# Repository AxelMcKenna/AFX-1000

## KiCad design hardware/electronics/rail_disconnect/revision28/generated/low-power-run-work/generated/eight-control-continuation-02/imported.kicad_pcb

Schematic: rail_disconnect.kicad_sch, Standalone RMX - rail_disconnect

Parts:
C1, C5, C9, C13, C17, C21, C25, C29, C34, C35, C36, C37, C57, C58, C59, C66, C67, C68, C69, C70, C71, C72, C73, C74, C75, C76, C77: 100nF 16V X7R; C_0805_2012Metric
C2, C3, C6, C7, C10, C11, C14, C15: 10pF 100V C0G 5%; C_0805_2012Metric
C4, C8: 1500uF 35V electrolytic 20% EEUFR1V152S; CP_Radial_D16.0mm_P7.50mm
C12, C16: 220uF 35V electrolytic 20% EEUFR1V221; CP_Radial_D8.0mm_P3.50mm
C20: 1500uF 16V electrolytic 20% EEUFR1C152; CP_Radial_D10.0mm_P5.00mm
C24: 4700uF 16V electrolytic 20% EEUFR1C472; CP_Radial_D16.0mm_P7.50mm
C26: 1uF 16V X7R; C_0805_2012Metric
C27, C28, C30, C31, C32, C33, C53, C54, C55, C56: 100pF 50V C0G 5%; C_0805_2012Metric
C38: 10uF 16V X7R; C_0805_2012Metric
C39, C41, C49, C61, C62, C63, C64, C65: 100nF 50V C0G 5% C1210C104J5GACTU; KEMET_C1210_LevelB
C40, C42, C44, C46, C48, C50, C52: 1uF 50V X7R; C_0805_2012Metric
C43, C45, C47, C51: 47nF 50V C0G 5% C1206C473J5GACTU; KEMET_C1206_LevelB
C60: 10nF 50V C0G 5%; C_0805_2012Metric
C78, C80, C81, C82, C83, C84, C85: 100nF 16V X7R 10% KEMET C0603C104K4RACTU; KEMET_C0603_LevelB
C79: 100nF 16V X7R 10% KEMET C0402C104K4RACTU; KEMET_C0402_LevelB
C86: 100nF 50V X7R C0603C104K5RACTU; AX03_C0603
J1, J3: Header6; PinHeader_1x06_P2.54mm_Vertical
J4: Alpha3079_AWG14_DIG_FORCE; AWG14_Force_2x1_P9mm_Engineering
J5, J6: Header3; PinHeader_1x03_P2.54mm_Vertical
J7, J8, J10, J11: 7466003R; 7466003R_M3_SMT_Annulus_NPTH
J9: E28 CONTROL; PinHeader_1x05_P2.54mm_Vertical
J12: JST B2B-PH-SM4-TB(LF)(SN); JST_B2B_PH_SM4_TB_MechanicalLands
Q1, Q2, Q3, Q4, Q5, Q6, Q7, Q8: CSD18540Q5B; CSD18540Q5B_TI_Q5B
R1, R9, R17, R25: 22 1%; R_0805_2012Metric
R2, R10, R18, R26, R60, R63, R68, R71, R76, R81, R86, R91: 20M 1%; R_0805_2012Metric
R3, R5, R11, R13, R19, R21, R27, R29, R61, R64, R69, R72, R77, R82, R87, R92: 10k 1%; R_0805_2012Metric
R4, R12, R20, R28, R98, R102, R106, R110, R114, R118, R122: 100 1%; R_0805_2012Metric
R6, R7, R14, R15, R22, R23, R30, R31: 15k 1%; R_0805_2012Metric
R8, R16, R24, R32, R40, R48: 47k 1%; R_0805_2012Metric
R49: 150k 0.01% 5ppm; R_0805_2012Metric
R50: 6.2k 0.01% 5ppm; R_0805_2012Metric
R51, R54, R58, R59, R62, R66, R67, R70, R74, R75, R79, R80, R84, R85, R89, R90, R94, R124, R127, R130, R133: 10k 0.01% 5ppm; R_0805_2012Metric
R52, R55: 1k 1%; R_0805_2012Metric
R53: 100k 0.01% 5ppm; R_0805_2012Metric
R56: 143k 0.01% 5ppm; R_0805_2012Metric
R57: 3.3k 0.01% 5ppm; R_0805_2012Metric
R65: 90.9k 0.01% 5ppm; R_0805_2012Metric
R73, R78: 31.6k 0.01% 5ppm; R_0805_2012Metric
R83: 12.4k 0.01% 5ppm; R_0805_2012Metric
R88: 7.5k 0.01% 5ppm; R_0805_2012Metric
R93: 200k 0.1% ERA6AEB204V - COMPLETE1% RECEIVING; R_0805_2012Metric
R95, R99, R103, R107, R111, R115, R119, R125, R128, R131, R134, R136, R141: 10k; R_0805_2012Metric
R96, R100, R104, R108, R112, R116, R120, R140: 47k; R_0805_2012Metric
R97, R101, R117: 2.43k 0.1%; R_0805_2012Metric
R105, R109, R113, R121: 604 0.1%; R_0805_2012Metric
R123, R126, R129, R132: 28.7k 0.01% 5ppm; R_0805_2012Metric
R135: 10k 0.1% 25ppm Panasonic ERA6AEB103V; Resistor_SMD_Panasonic_ERA6A_2012
R137: 11.1k 0.1%; R_0805_2012Metric
R138: 39.2 0.1%; R_0805_2012Metric
R139: 10k 0.1%; R_0805_2012Metric
R142: 15k; R_0805_2012Metric
R143: 15k 0.1% 25ppm Panasonic ERA6AEB153V; Resistor_SMD_Panasonic_ERA6A_2012
U1, U2, U3, U4: SI8751AB-ISR; SOIC-8_3.9x4.9mm_P1.27mm
U7: REF35125QDBVR; SOT-23-6
U8: OPA2333AID; SOIC-8_3.9x4.9mm_P1.27mm
U9, U10: TLV1824DR; SOIC-14_3.9x8.7mm_P1.27mm
U11, U12, U24, U25, U26, U27: SN74LVC08APWR; TSSOP-14_4.4x5mm_P0.65mm
U13, U14, U15, U16, U17, U32, U33: TPS259482LYWP; TPS259482L_YWP0012A
U18: TLV1824PWR; TLV1824_PW0014A
U19, U20: TPS389001DSET; TPS389001_DSE0006A
U21, U22: SN74LVC02APWR; TSSOP-14_4.4x5mm_P0.65mm
U23: SN74LVC32APWR; TSSOP-14_4.4x5mm_P0.65mm
U28: SN74LVC14APWR; SN74LVC14A_PW0014A
U29, U30, U31, U34: SN74AUP2G08DCUR; SN74AUP2G08_DCU0008A
U35, U36, U37, U38, U39, U40, U41, U42: SN74AUP3G17DCUR; SN74LVC3G17_DCU0008A
U43: SN74AUP1G17DCKR; AX03_DCK0005A

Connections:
/5V_DIG: C24.1, J4.1 (5V_DIG), R48.1, R132.1, U15.6 (OUT), U15.11 (OUT), U16.6 (OUT), U16.11 (OUT), U17.6 (OUT), U17.11 (OUT), U33.6 (OUT), U33.11 (OUT)
/5V_DIG_OV_OK: R81.1, R82.2, U10.1 (2OUT), U37.6 (3A)
/5V_DIG_OV_OK_SCHMITT: U11.10 (3B), U37.2 (3Y)
/5V_DIG_OV_REF: R80.2, R81.2, U10.7 (2+)
/5V_DIG_OV_SENSE: C33.1, R78.2, R79.1, U10.6 (2-)
/5V_DIG_SRC: C44.1, C46.1, C48.1, C52.1, J11.1, R78.1, R126.1, U15.5 (IN), U15.12 (IN), U16.5 (IN), U16.12 (IN), U17.5 (IN), U17.12 (IN), U33.5 (IN), U33.12 (IN)
/AGND: C1.2, C4.2, C5.2, C8.1, C9.2, C12.2, C13.2, C16.1, C17.2, C20.2, C21.2, C24.2, C25.2, C26.2, C27.2, C28.2, C29.2, C30.2, C31.2, C32.2, C33.2, C34.2, C35.2, C36.2, C37.2, C38.2, C39.2, C40.2, C41.2, C42.2, C43.2, C44.2, C45.2, C46.2, C47.2, C48.2, C49.2, C50.2, C51.2, C52.2, C53.2, C54.2, C55.2, C56.2, C57.2, C58.2, C59.2, C60.2, C61.2, C62.2, C63.2, C64.2, C65.2, C66.2, C67.2, C68.2, C69.2, C70.2, C71.2, C72.2, C73.2, C74.2, C75.2, C76.2, C77.2, C78.2, C79.2, C80.2, C81.2, C82.2, C83.2, C84.2, C85.2, C86.2, J1.2 (AGND), J3.2 (AGND), J4.2 (AGND), J5.2 (AGND), J6.1 (AGND), J7.1, J8.1, J9.1 (AGND), J12.2 (AGND), R3.2, R5.2, R8.2, R11.2, R13.2, R16.2, R19.2, R21.2, R24.2, R27.2, R29.2, R32.2, R40.2, R48.2, R58.2, R66.2, R74.2, R79.2, R84.2, R89.2, R93.2, R94.2, R96.2, R97.2, R100.2, R101.2, R104.2, R105.2, R108.2, R109.2, R112.2, R113.2, R116.2, R117.2, R120.2, R121.2, R124.2, R127.2, R130.2, R133.2, R139.2, R140.2, R141.2, R142.2, R143.2, U1.4 (GND), U2.4 (GND), U3.4 (GND), U4.4 (GND), U7.1 (GND), U7.2 (GND), U8.3 (IN+_A), U8.4 (V-), U8.5 (IN+_B), U9.12 (V-), U10.12 (V-), U11.7 (GND), U12.7 (GND), U13.2 (OVLO), U13.4 (RCBCTRL), U13.8 (GND), U14.2 (OVLO), U14.4 (RCBCTRL), U14.8 (GND), U15.2 (OVLO), U15.4 (RCBCTRL), U15.8 (GND), U16.2 (OVLO), U16.4 (RCBCTRL), U16.8 (GND), U17.2 (OVLO), U17.4 (RCBCTRL), U17.8 (GND), U18.12 (V-), U19.2 (GND), U20.2 (GND), U21.7 (GND), U22.7 (GND), U22.9 (B), U22.12 (B), U23.7 (GND), U24.7 (GND), U25.7 (GND), U26.7 (GND), U27.7 (GND), U28.7 (GND), U29.4 (GND), U30.4 (GND), U31.4 (GND), U32.2 (OVLO), U32.4 (RCBCTRL), U32.8 (GND), U33.2 (OVLO), U33.4 (RCBCTRL), U33.8 (GND), U34.4 (GND), U35.4 (GND), U36.4 (GND), U37.4 (GND), U38.4 (GND), U39.4 (GND), U40.4 (GND), U41.4 (GND), U42.3 (2A), U42.4 (GND), U42.6 (3A), U43.3 (GND)
/ALL_RAILS_ALLOW: U12.11 (4Y), U21.2 (A), U29.1 (A)
/ANA_OUTPUT_OK: R131.2, U18.14 (UV_OK), U39.3 (2A)
/ANA_OUTPUT_OK_SCHMITT: U24.4 (A), U39.5 (2Y)
/ANA_PG0: R95.1, U13.3 (SPLYGD), U41.3 (2A)
/ANA_PG0_SCHMITT: U31.2 (B), U41.5 (2Y)
/ANA_PG1: R99.1, U14.3 (SPLYGD), U41.6 (3A)
/ANA_PG1_SCHMITT: U34.6 (B), U41.2 (3Y)
/ANA_PG2: R115.1, U32.3 (SPLYGD), U42.1 (1A)
/ANA_PG2_SCHMITT: U26.10 (B), U42.7 (1Y)
/ANA_SOURCE_OK: R125.2, U18.2 (UV_OK), U38.6 (3A)
/ANA_SOURCE_OK_SCHMITT: U24.1 (A), U38.2 (3Y)
/DIG_OUTPUT_OK: R134.2, U18.13 (UV_OK), U39.6 (3A)
/DIG_OUTPUT_OK_SCHMITT: U24.5 (B), U39.2 (3Y)
/DIG_PG0: R103.1, U15.3 (SPLYGD), U40.1 (1A)
/DIG_PG0_SCHMITT: U29.6 (B), U40.7 (1Y)
/DIG_PG1: R107.1, U16.3 (SPLYGD), U40.3 (2A)
/DIG_PG1_SCHMITT: U30.2 (B), U40.5 (2Y)
/DIG_PG2: R111.1, U17.3 (SPLYGD), U40.6 (3A)
/DIG_PG2_SCHMITT: U34.1 (A), U40.2 (3Y)
/DIG_PG3: R119.1, U33.3 (SPLYGD), U41.1 (1A)
/DIG_PG3_SCHMITT: U26.9 (A), U30.6 (B), U41.7 (1Y)
/DIG_SOURCE_OK: R128.2, U18.1 (UV_OK), U39.1 (1A)
/DIG_SOURCE_OK_SCHMITT: U24.2 (B), U39.7 (1Y)
/E28_ALL_CHANNELS_READY: U26.8 (Y), U26.12 (A)
/E28_ANA_0_DVDT: R98.1, U13.7 (DVDT)
/E28_ANA_0_DVDT_CAP: C39.1, R98.2
/E28_ANA_0_ILM: R97.1, U13.9 (ILM)
/E28_ANA_1_DVDT: R102.1, U14.7 (DVDT)
/E28_ANA_1_DVDT_CAP: C41.1, R102.2
/E28_ANA_1_ILM: R101.1, U14.9 (ILM)
/E28_ANA_2_DVDT: R118.1, U32.7 (DVDT)
/E28_ANA_2_DVDT_CAP: C49.1, R118.2
/E28_ANA_2_ILM: R117.1, U32.9 (ILM)
/E28_ANA_ENABLE: R96.1, U13.1 (EN_UVLO), U30.3 (Y)
/E28_ANA_FOLLOW: R100.1, U14.1 (EN_UVLO), U31.7 (Y)
/E28_ANA_FOLLOW2: R116.1, U32.1 (EN_UVLO), U34.3 (Y)
/E28_ANA_OUT_SENSE: C55.1, R129.2, R130.1, U18.9 (SENSE+)
/E28_ANA_SRC_SENSE: C53.1, R123.2, R124.1, U18.5 (SENSE+)
/E28_ARMED: U21.3 (B), U21.4 (Y), U25.9 (A)
/E28_ARM_BAR: U21.1 (Y), U21.6 (B)
/E28_AUX_CT: C60.1, U19.5 (CT)
/E28_AUX_DIV: R137.2, R138.1
/E28_AUX_RESET_N: U31.5 (A), U35.5 (2Y)
/E28_AUX_RESET_RAW: R135.1, U19.6 (RESET_N), U35.3 (2A)
/E28_AUX_SENSE: R138.2, R139.1, U19.1 (SENSE)
/E28_AUX_VALID: U24.13 (B), U28.3 (A), U29.2 (B), U31.3 (Y)
/E28_DIG_0_DVDT: R106.1, U15.7 (DVDT)
/E28_DIG_0_DVDT_CAP: C43.1, R106.2
/E28_DIG_0_ILM: R105.1, U15.9 (ILM)
/E28_DIG_1_DVDT: R110.1, U16.7 (DVDT)
/E28_DIG_1_DVDT_CAP: C45.1, R110.2
/E28_DIG_1_ILM: R109.1, U16.9 (ILM)
/E28_DIG_2_DVDT: R114.1, U17.7 (DVDT)
/E28_DIG_2_DVDT_CAP: C47.1, R114.2
/E28_DIG_2_ILM: R113.1, U17.9 (ILM)
/E28_DIG_3_DVDT: R122.1, U33.7 (DVDT)
/E28_DIG_3_DVDT_CAP: C51.1, R122.2
/E28_DIG_3_ILM: R121.1, U33.9 (ILM)
/E28_DIG_FOLLOW1: R108.1, U16.1 (EN_UVLO), U29.3 (Y)
/E28_DIG_FOLLOW2: R112.1, U17.1 (EN_UVLO), U30.7 (Y)
/E28_DIG_FOLLOW3: R120.1, U33.1 (EN_UVLO), U34.7 (Y)
/E28_DIG_OUT_SENSE: C56.1, R132.2, R133.1, U18.11 (SENSE+)
/E28_DIG_SRC_SENSE: C54.1, R126.2, R127.1, U18.7 (SENSE+)
/E28_FAULT: J9.4 (E28_FAULT), U21.9 (B), U21.13 (Y), U23.5 (B), U28.5 (A)
/E28_FAULT_A: U23.8 (Y), U23.12 (A)
/E28_FAULT_ANY: U23.11 (Y), U25.10 (B)
/E28_FAULT_BAR: U21.10 (Y), U21.12 (B)
/E28_FAULT_SET: U21.8 (A), U25.8 (Y)
/E28_MASTER_ENABLE: J6.2 (ALL_RAILS_ALLOW), J9.5 (E28_MASTER_ENABLE), R4.1, R12.1, R20.1, R28.1, R104.1, R141.1, U15.1 (EN_UVLO), U20.1 (SENSE), U20.3 (MR_N), U25.13 (B), U27.2 (B), U29.5 (A), U29.7 (Y), U30.1 (A), U30.5 (A), U31.1 (A), U34.2 (B), U34.5 (A)
/E28_NORMAL_OK: U22.8 (A), U27.8 (Y)
/E28_NORMAL_PRE: U24.8 (Y), U27.9 (A)
/E28_NOT_AUX: U23.2 (B), U28.4 (Y)
/E28_NOT_FAULT: U27.13 (B), U28.6 (Y)
/E28_NOT_NORMAL_OK: U22.10 (Y), U23.9 (A)
/E28_NOT_OUT_READY: U22.13 (Y), U26.2 (B), U26.5 (B)
/E28_NOT_RUN: U23.1 (A), U28.2 (Y), U28.9 (A)
/E28_NOT_SOURCE_READY: U28.10 (Y), U28.13 (A)
/E28_OUTPUT_PERMISSION: U26.11 (Y), U27.1 (A)
/E28_OUTPUT_READY: J9.3 (E28_OUTPUT_READY), U25.6 (Y)
/E28_OUT_ARMED: U22.3 (B), U22.4 (Y), U26.1 (A)
/E28_OUT_ARM_BAR: U22.1 (Y), U22.6 (B)
/E28_OUT_READY: U22.11 (A), U24.6 (Y), U25.12 (A), U26.13 (B)
/E28_OUT_UV_FAULT: U23.10 (B), U26.3 (Y)
/E28_OUT_VALID_ACTIVE: U22.2 (A), U25.11 (Y)
/E28_RESET: U21.5 (A), U21.11 (A), U23.3 (Y), U23.4 (A)
/E28_RESET_OUT: U22.5 (A), U23.6 (Y)
/E28_RUN_AND_SOURCE: U24.12 (A), U27.6 (Y)
/E28_RUN_LOGIC: U27.4 (A), U28.8 (Y)
/E28_SAFE_REQUEST: R140.1, U12.13 (4B), U27.11 (Y)
/E28_SAFE_STAGE: U25.3 (Y), U27.12 (A)
/E28_SOURCE_READY: U24.3 (Y), U24.9 (A), U25.2 (B)
/E28_SOURCE_READY_LOGIC: U27.5 (B), U27.10 (B), U28.12 (Y)
/E28_TIMEOUT: U26.4 (A), U35.7 (1Y)
/E28_TIMEOUT_CT: C61.1, C62.1, C63.1, C64.1, C65.1, U20.5 (CT)
/E28_TIMEOUT_FAULT: U23.13 (B), U26.6 (Y)
/E28_TIMEOUT_RAW: R136.1, U20.6 (RESET_N), U35.1 (1A)
/E28_USER_AUX: U24.11 (Y), U25.1 (A)
/N12: C16.2, J3.5 (N12), Q8.3 (DRAIN_GROUP), R31.1, R32.1
/N12_ALLOW: R28.2, R29.1, U4.3 (IN)
/N12_COMMON: Q7.1 (SOURCE_GROUP), Q8.1 (SOURCE_GROUP), R26.2, U4.5 (SOURCE)
/N12_DRIVE: R25.1, U4.8 (GATE)
/N12_GATE: Q7.2 (GATE_GROUP), Q8.2 (GATE_GROUP), R25.2, R26.1
/N12_INV: R54.1, R55.1, U8.7 (OUT_B)
/N12_MCAP1: C14.2, U4.7 (MCAP1)
/N12_MCAP1_LIMIT: C14.1, R30.2
/N12_MCAP2: C15.2, U4.6 (MCAP2)
/N12_MCAP2_LIMIT: C15.1, R31.2
/N12_OV_OK: R71.1, R72.2, U9.13 (4OUT), U37.1 (1A)
/N12_OV_OK_SCHMITT: U11.4 (2A), U37.7 (1Y)
/N12_OV_REF: R70.2, R71.2, U9.11 (4+)
/N12_OV_SENSE: C28.1, R55.2, U9.10 (4-)
/N12_SRC: J1.5 (N12_SRC), Q7.3 (DRAIN_GROUP), R30.1, R53.1
/N12_SUM: R53.2, R54.2, U8.6 (IN-_B)
/N12_TT: R27.1, U4.2 (TT)
/N19: C8.2, J3.3 (N19), Q4.3 (DRAIN_GROUP), R15.1, R16.1
/N19_ALLOW: R12.2, R13.1, U2.3 (IN)
/N19_COMMON: Q3.1 (SOURCE_GROUP), Q4.1 (SOURCE_GROUP), R10.2, U2.5 (SOURCE)
/N19_DRIVE: R9.1, U2.8 (GATE)
/N19_GATE: Q3.2 (GATE_GROUP), Q4.2 (GATE_GROUP), R9.2, R10.1
/N19_INPUT_MID: R49.2, R50.1
/N19_INV: R51.1, R52.1, U8.1 (OUT_A)
/N19_MCAP1: C6.2, U2.7 (MCAP1)
/N19_MCAP1_LIMIT: C6.1, R14.2
/N19_MCAP2: C7.2, U2.6 (MCAP2)
/N19_MCAP2_LIMIT: C7.1, R15.2
/N19_OV_OK: R63.1, R64.2, U9.1 (2OUT), U36.3 (2A)
/N19_OV_OK_SCHMITT: U11.1 (1A), U36.5 (2Y)
/N19_OV_REF: R62.2, R63.2, U9.7 (2+)
/N19_OV_SENSE: C27.1, R52.2, U9.6 (2-)
/N19_SRC: J1.3 (N19_SRC), Q3.3 (DRAIN_GROUP), R14.1, R49.1
/N19_SUM: R50.2, R51.2, U8.2 (IN-_A)
/N19_TT: R11.1, U2.2 (TT)
/NF_OUTPUT_VALID_RAW: J12.1 (NF_OUTPUT_VALID_RAW), R143.1, U35.6 (3A)
/NF_VALID_LOGIC: U25.5 (B), U35.2 (3Y)
/OK_5: U11.8 (3Y), U12.4 (2A)
/OK_12: U11.6 (2Y), U12.2 (1B)
/OK_19: U11.3 (1Y), U12.1 (1A)
/OK_ALL_OV: U12.8 (3Y), U12.12 (4A), U24.10 (B)
/OK_ANALOG: U12.3 (1Y), U12.9 (3A)
/OK_AUXILIARY: U12.6 (2Y), U12.10 (3B)
/OK_REF: U11.11 (4Y), U12.5 (2B)
/P03_SOURCES_READY: J9.2 (P03_SOURCES_READY), R142.1, U28.11 (A)
/P12: C12.1, J3.4 (P12), Q6.3 (DRAIN_GROUP), R23.1, R24.1
/P12_ALLOW: R20.2, R21.1, U3.3 (IN)
/P12_COMMON: Q5.1 (SOURCE_GROUP), Q6.1 (SOURCE_GROUP), R18.2, U3.5 (SOURCE)
/P12_DRIVE: R17.1, U3.8 (GATE)
/P12_GATE: Q5.2 (GATE_GROUP), Q6.2 (GATE_GROUP), R17.2, R18.1
/P12_MCAP1: C10.2, U3.7 (MCAP1)
/P12_MCAP1_LIMIT: C10.1, R22.2
/P12_MCAP2: C11.2, U3.6 (MCAP2)
/P12_MCAP2_LIMIT: C11.1, R23.2
/P12_OV_OK: R68.1, R69.2, U9.14 (3OUT), U36.6 (3A)
/P12_OV_OK_SCHMITT: U11.5 (2B), U36.2 (3Y)
/P12_OV_REF: R67.2, R68.2, U9.9 (3+)
/P12_OV_SENSE: C31.1, R65.2, R66.1, U9.8 (3-)
/P12_SRC: J1.4 (P12_SRC), Q5.3 (DRAIN_GROUP), R22.1, R65.1
/P12_TT: R19.1, U3.2 (TT)
/P19: C4.1, J3.1 (P19), Q2.3 (DRAIN_GROUP), R7.1, R8.1
/P19_ALLOW: R4.2, R5.1, U1.3 (IN)
/P19_COMMON: Q1.1 (SOURCE_GROUP), Q2.1 (SOURCE_GROUP), R2.2, U1.5 (SOURCE)
/P19_DRIVE: R1.1, U1.8 (GATE)
/P19_GATE: Q1.2 (GATE_GROUP), Q2.2 (GATE_GROUP), R1.2, R2.1
/P19_MCAP1: C2.2, U1.7 (MCAP1)
/P19_MCAP1_LIMIT: C2.1, R6.2
/P19_MCAP2: C3.2, U1.6 (MCAP2)
/P19_MCAP2_LIMIT: C3.1, R7.2
/P19_OV_OK: R60.1, R61.2, U9.2 (1OUT), U36.1 (1A)
/P19_OV_OK_SCHMITT: U11.2 (1B), U36.7 (1Y)
/P19_OV_REF: R59.2, R60.2, U9.5 (1+)
/P19_OV_SENSE: C30.1, R57.2, R58.1, U9.4 (1-)
/P19_SENSE_MID: R56.2, R57.1
/P19_SRC: J1.1 (P19_SRC), Q1.3 (DRAIN_GROUP), R6.1, R56.1
/P19_TT: R3.1, U1.2 (TT)
/POS_OUTPUT_READY: U25.4 (A), U27.3 (Y)
/POWER_RUN: J5.3 (POWER_RUN), R93.1, U43.2 (A)
/PROTECT_REF: C26.1, J6.3 (PROTECT_REF), R59.1, R62.1, R67.1, R70.1, R75.1, R80.1, R85.1, R94.1, U7.6 (VREF), U10.10 (4-), U18.4 (REF-), U18.6 (REF-), U18.8 (REF-), U18.10 (REF-)
/REF_HIGH_AUX: R88.2, R89.1, R90.1
/REF_HIGH_OK: R91.1, R92.2, U10.13 (4OUT), U38.3 (2A)
/REF_HIGH_OK_SCHMITT: U11.13 (4B), U38.5 (2Y)
/REF_HIGH_POSITIVE: R90.2, R91.2, U10.11 (4+)
/REF_LOW_AUX: R83.2, R84.1, U10.8 (3-)
/REF_LOW_OK: R86.1, R87.2, U10.14 (3OUT), U38.1 (1A)
/REF_LOW_OK_SCHMITT: U11.12 (4A), U38.7 (1Y)
/REF_LOW_POSITIVE: R85.2, R86.2, U10.9 (3+)
/RUN_BUFFERED: U28.1 (A), U43.4 (Y)
/V2V5_AUX: C1.1, C5.1, C9.1, C13.1, C17.1, C21.1, C25.1, C29.1, C34.1, C35.1, C36.1, C37.1, C38.1, C57.1, C58.1, C59.1, C66.1, C67.1, C68.1, C69.1, C70.1, C71.1, C72.1, C73.1, C74.1, C75.1, C76.1, C77.1, C78.1, C79.1, C80.1, C81.1, C82.1, C83.1, C84.1, C85.1, C86.1, J5.1 (V2V5_AUX), R61.1, R64.1, R69.1, R72.1, R77.1, R82.1, R83.1, R87.1, R88.1, R92.1, R95.2, R99.2, R103.2, R107.2, R111.2, R115.2, R119.2, R125.1, R128.1, R131.1, R134.1, R135.2, R136.2, R137.1, U1.1 (VDD), U2.1 (VDD), U3.1 (VDD), U4.1 (VDD), U7.3 (EN), U7.4 (VIN), U8.8 (V+), U9.3 (V+), U10.3 (V+), U11.14 (VCC), U12.14 (VCC), U18.3 (V+), U19.3 (MR_N), U19.4 (VDD), U20.4 (VDD), U21.14 (VCC), U22.14 (VCC), U23.14 (VCC), U24.14 (VCC), U25.14 (VCC), U26.14 (VCC), U27.14 (VCC), U28.14 (VCC), U29.8 (VCC), U30.8 (VCC), U31.6 (B), U31.8 (VCC), U34.8 (VCC), U35.8 (VCC), U36.8 (VCC), U37.8 (VCC), U38.8 (VCC), U39.8 (VCC), U40.8 (VCC), U41.8 (VCC), U42.8 (VCC), U43.5 (VCC)
/V5_REG: C20.1, J3.6 (V5_REG), R40.1, R129.1, U13.6 (OUT), U13.11 (OUT), U14.6 (OUT), U14.11 (OUT), U32.6 (OUT), U32.11 (OUT)
/V5_REG_OV_OK: R76.1, R77.2, U10.2 (1OUT), U37.3 (2A)
/V5_REG_OV_OK_SCHMITT: U11.9 (3A), U37.5 (2Y)
/V5_REG_OV_REF: R75.2, R76.2, U10.5 (1+)
/V5_REG_OV_SENSE: C32.1, R73.2, R74.1, U10.4 (1-)
/V5_REG_SRC: C40.1, C42.1, C50.1, J1.6 (V5_REG_SRC), J10.1, R73.1, R123.1, U13.5 (IN), U13.12 (IN), U14.5 (IN), U14.12 (IN), U32.5 (IN), U32.12 (IN)

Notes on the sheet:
E28LP lowpowerRUN prototype; original force/timing/latch topology retained; physical validation unfinished.

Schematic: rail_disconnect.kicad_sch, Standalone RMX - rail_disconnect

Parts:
C1, C5, C9, C13, C17, C21, C25, C29, C34, C35, C36, C37, C57, C58, C59, C66, C67, C68, C69, C70, C71, C72, C73, C74, C75, C76, C77: 100nF 16V X7R; C_0805_2012Metric
C2, C3, C6, C7, C10, C11, C14, C15: 10pF 100V C0G 5%; C_0805_2012Metric
C4, C8: 1500uF 35V electrolytic 20% EEUFR1V152S; CP_Radial_D16.0mm_P7.50mm
C12, C16: 220uF 35V electrolytic 20% EEUFR1V221; CP_Radial_D8.0mm_P3.50mm
C20: 1500uF 16V electrolytic 20% EEUFR1C152; CP_Radial_D10.0mm_P5.00mm
C24: 4700uF 16V electrolytic 20% EEUFR1C472; CP_Radial_D16.0mm_P7.50mm
C26: 1uF 16V X7R; C_0805_2012Metric
C27, C28, C30, C31, C32, C33, C53, C54, C55, C56: 100pF 50V C0G 5%; C_0805_2012Metric
C38: 10uF 16V X7R; C_0805_2012Metric
C39, C41, C49, C61, C62, C63, C64, C65: 100nF 50V C0G 5% C1210C104J5GACTU; KEMET_C1210_LevelB
C40, C42, C44, C46, C48, C50, C52: 1uF 50V X7R; C_0805_2012Metric
C43, C45, C47, C51: 47nF 50V C0G 5% C1206C473J5GACTU; KEMET_C1206_LevelB
C60: 10nF 50V C0G 5%; C_0805_2012Metric
C78, C80, C81, C82, C83, C84, C85: 100nF 16V X7R 10% KEMET C0603C104K4RACTU; KEMET_C0603_LevelB
C79: 100nF 16V X7R 10% KEMET C0402C104K4RACTU; KEMET_C0402_LevelB
C86: 100nF 50V X7R C0603C104K5RACTU; AX03_C0603
J1, J3: Header6; PinHeader_1x06_P2.54mm_Vertical
J4: Alpha3079_AWG14_DIG_FORCE; AWG14_Force_2x1_P9mm_Engineering
J5, J6: Header3; PinHeader_1x03_P2.54mm_Vertical
J7, J8, J10, J11: 7466003R; 7466003R_M3_SMT_Annulus_NPTH
J9: E28 CONTROL; PinHeader_1x05_P2.54mm_Vertical
J12: JST B2B-PH-SM4-TB(LF)(SN); JST_B2B_PH_SM4_TB_MechanicalLands
Q1, Q2, Q3, Q4, Q5, Q6, Q7, Q8: CSD18540Q5B; CSD18540Q5B_TI_Q5B
R1, R9, R17, R25: 22 1%; R_0805_2012Metric
R2, R10, R18, R26, R60, R63, R68, R71, R76, R81, R86, R91: 20M 1%; R_0805_2012Metric
R3, R5, R11, R13, R19, R21, R27, R29, R61, R64, R69, R72, R77, R82, R87, R92: 10k 1%; R_0805_2012Metric
R4, R12, R20, R28, R98, R102, R106, R110, R114, R118, R122: 100 1%; R_0805_2012Metric
R6, R7, R14, R15, R22, R23, R30, R31: 15k 1%; R_0805_2012Metric
R8, R16, R24, R32, R40, R48: 47k 1%; R_0805_2012Metric
R49: 150k 0.01% 5ppm; R_0805_2012Metric
R50: 6.2k 0.01% 5ppm; R_0805_2012Metric
R51, R54, R58, R59, R62, R66, R67, R70, R74, R75, R79, R80, R84, R85, R89, R90, R94, R124, R127, R130, R133: 10k 0.01% 5ppm; R_0805_2012Metric
R52, R55: 1k 1%; R_0805_2012Metric
R53: 100k 0.01% 5ppm; R_0805_2012Metric
R56: 143k 0.01% 5ppm; R_0805_2012Metric
R57: 3.3k 0.01% 5ppm; R_0805_2012Metric
R65: 90.9k 0.01% 5ppm; R_0805_2012Metric
R73, R78: 31.6k 0.01% 5ppm; R_0805_2012Metric
R83: 12.4k 0.01% 5ppm; R_0805_2012Metric
R88: 7.5k 0.01% 5ppm; R_0805_2012Metric
R93: 200k 0.1% ERA6AEB204V - COMPLETE1% RECEIVING; R_0805_2012Metric
R95, R99, R103, R107, R111, R115, R119, R125, R128, R131, R134, R136, R141: 10k; R_0805_2012Metric
R96, R100, R104, R108, R112, R116, R120, R140: 47k; R_0805_2012Metric
R97, R101, R117: 2.43k 0.1%; R_0805_2012Metric
R105, R109, R113, R121: 604 0.1%; R_0805_2012Metric
R123, R126, R129, R132: 28.7k 0.01% 5ppm; R_0805_2012Metric
R135: 10k 0.1% 25ppm Panasonic ERA6AEB103V; Resistor_SMD_Panasonic_ERA6A_2012
R137: 11.1k 0.1%; R_0805_2012Metric
R138: 39.2 0.1%; R_0805_2012Metric
R139: 10k 0.1%; R_0805_2012Metric
R142: 15k; R_0805_2012Metric
R143: 15k 0.1% 25ppm Panasonic ERA6AEB153V; Resistor_SMD_Panasonic_ERA6A_2012
U1, U2, U3, U4: SI8751AB-ISR; SOIC-8_3.9x4.9mm_P1.27mm
U7: REF35125QDBVR; SOT-23-6
U8: OPA2333AID; SOIC-8_3.9x4.9mm_P1.27mm
U9, U10: TLV1824DR; SOIC-14_3.9x8.7mm_P1.27mm
U11, U12, U24, U25, U26, U27: SN74LVC08APWR; TSSOP-14_4.4x5mm_P0.65mm
U13, U14, U15, U16, U17, U32, U33: TPS259482LYWP; TPS259482L_YWP0012A
U18: TLV1824PWR; TLV1824_PW0014A
U19, U20: TPS389001DSET; TPS389001_DSE0006A
U21, U22: SN74LVC02APWR; TSSOP-14_4.4x5mm_P0.65mm
U23: SN74LVC32APWR; TSSOP-14_4.4x5mm_P0.65mm
U28: SN74LVC14APWR; SN74LVC14A_PW0014A
U29, U30, U31, U34: SN74AUP2G08DCUR; SN74AUP2G08_DCU0008A
U35, U36, U37, U38, U39, U40, U41, U42: SN74AUP3G17DCUR; SN74LVC3G17_DCU0008A
U43: SN74AUP1G17DCKR; AX03_DCK0005A

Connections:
/5V_DIG: C24.1, J4.1 (5V_DIG), R48.1, R132.1, U15.6 (OUT), U15.11 (OUT), U16.6 (OUT), U16.11 (OUT), U17.6 (OUT), U17.11 (OUT), U33.6 (OUT), U33.11 (OUT)
/5V_DIG_OV_OK: R81.1, R82.2, U10.1 (2OUT), U37.6 (3A)
/5V_DIG_OV_OK_SCHMITT: U11.10 (3B), U37.2 (3Y)
/5V_DIG_OV_REF: R80.2, R81.2, U10.7 (2+)
/5V_DIG_OV_SENSE: C33.1, R78.2, R79.1, U10.6 (2-)
/5V_DIG_SRC: C44.1, C46.1, C48.1, C52.1, J11.1, R78.1, R126.1, U15.5 (IN), U15.12 (IN), U16.5 (IN), U16.12 (IN), U17.5 (IN), U17.12 (IN), U33.5 (IN), U33.12 (IN)
/AGND: C1.2, C4.2, C5.2, C8.1, C9.2, C12.2, C13.2, C16.1, C17.2, C20.2, C21.2, C24.2, C25.2, C26.2, C27.2, C28.2, C29.2, C30.2, C31.2, C32.2, C33.2, C34.2, C35.2, C36.2, C37.2, C38.2, C39.2, C40.2, C41.2, C42.2, C43.2, C44.2, C45.2, C46.2, C47.2, C48.2, C49.2, C50.2, C51.2, C52.2, C53.2, C54.2, C55.2, C56.2, C57.2, C58.2, C59.2, C60.2, C61.2, C62.2, C63.2, C64.2, C65.2, C66.2, C67.2, C68.2, C69.2, C70.2, C71.2, C72.2, C73.2, C74.2, C75.2, C76.2, C77.2, C78.2, C79.2, C80.2, C81.2, C82.2, C83.2, C84.2, C85.2, C86.2, J1.2 (AGND), J3.2 (AGND), J4.2 (AGND), J5.2 (AGND), J6.1 (AGND), J7.1, J8.1, J9.1 (AGND), J12.2 (AGND), R3.2, R5.2, R8.2, R11.2, R13.2, R16.2, R19.2, R21.2, R24.2, R27.2, R29.2, R32.2, R40.2, R48.2, R58.2, R66.2, R74.2, R79.2, R84.2, R89.2, R93.2, R94.2, R96.2, R97.2, R100.2, R101.2, R104.2, R105.2, R108.2, R109.2, R112.2, R113.2, R116.2, R117.2, R120.2, R121.2, R124.2, R127.2, R130.2, R133.2, R139.2, R140.2, R141.2, R142.2, R143.2, U1.4 (GND), U2.4 (GND), U3.4 (GND), U4.4 (GND), U7.1 (GND), U7.2 (GND), U8.3 (IN+_A), U8.4 (V-), U8.5 (IN+_B), U9.12 (V-), U10.12 (V-), U11.7 (GND), U12.7 (GND), U13.2 (OVLO), U13.4 (RCBCTRL), U13.8 (GND), U14.2 (OVLO), U14.4 (RCBCTRL), U14.8 (GND), U15.2 (OVLO), U15.4 (RCBCTRL), U15.8 (GND), U16.2 (OVLO), U16.4 (RCBCTRL), U16.8 (GND), U17.2 (OVLO), U17.4 (RCBCTRL), U17.8 (GND), U18.12 (V-), U19.2 (GND), U20.2 (GND), U21.7 (GND), U22.7 (GND), U22.9 (B), U22.12 (B), U23.7 (GND), U24.7 (GND), U25.7 (GND), U26.7 (GND), U27.7 (GND), U28.7 (GND), U29.4 (GND), U30.4 (GND), U31.4 (GND), U32.2 (OVLO), U32.4 (RCBCTRL), U32.8 (GND), U33.2 (OVLO), U33.4 (RCBCTRL), U33.8 (GND), U34.4 (GND), U35.4 (GND), U36.4 (GND), U37.4 (GND), U38.4 (GND), U39.4 (GND), U40.4 (GND), U41.4 (GND), U42.3 (2A), U42.4 (GND), U42.6 (3A), U43.3 (GND)
/ALL_RAILS_ALLOW: U12.11 (4Y), U21.2 (A), U29.1 (A)
/ANA_OUTPUT_OK: R131.2, U18.14 (UV_OK), U39.3 (2A)
/ANA_OUTPUT_OK_SCHMITT: U24.4 (A), U39.5 (2Y)
/ANA_PG0: R95.1, U13.3 (SPLYGD), U41.3 (2A)
/ANA_PG0_SCHMITT: U31.2 (B), U41.5 (2Y)
/ANA_PG1: R99.1, U14.3 (SPLYGD), U41.6 (3A)
/ANA_PG1_SCHMITT: U34.6 (B), U41.2 (3Y)
/ANA_PG2: R115.1, U32.3 (SPLYGD), U42.1 (1A)
/ANA_PG2_SCHMITT: U26.10 (B), U42.7 (1Y)
/ANA_SOURCE_OK: R125.2, U18.2 (UV_OK), U38.6 (3A)
/ANA_SOURCE_OK_SCHMITT: U24.1 (A), U38.2 (3Y)
/DIG_OUTPUT_OK: R134.2, U18.13 (UV_OK), U39.6 (3A)
/DIG_OUTPUT_OK_SCHMITT: U24.5 (B), U39.2 (3Y)
/DIG_PG0: R103.1, U15.3 (SPLYGD), U40.1 (1A)
/DIG_PG0_SCHMITT: U29.6 (B), U40.7 (1Y)
/DIG_PG1: R107.1, U16.3 (SPLYGD), U40.3 (2A)
/DIG_PG1_SCHMITT: U30.2 (B), U40.5 (2Y)
/DIG_PG2: R111.1, U17.3 (SPLYGD), U40.6 (3A)
/DIG_PG2_SCHMITT: U34.1 (A), U40.2 (3Y)
/DIG_PG3: R119.1, U33.3 (SPLYGD), U41.1 (1A)
/DIG_PG3_SCHMITT: U26.9 (A), U30.6 (B), U41.7 (1Y)
/DIG_SOURCE_OK: R128.2, U18.1 (UV_OK), U39.1 (1A)
/DIG_SOURCE_OK_SCHMITT: U24.2 (B), U39.7 (1Y)
/E28_ALL_CHANNELS_READY: U26.8 (Y), U26.12 (A)
/E28_ANA_0_DVDT: R98.1, U13.7 (DVDT)
/E28_ANA_0_DVDT_CAP: C39.1, R98.2
/E28_ANA_0_ILM: R97.1, U13.9 (ILM)
/E28_ANA_1_DVDT: R102.1, U14.7 (DVDT)
/E28_ANA_1_DVDT_CAP: C41.1, R102.2
/E28_ANA_1_ILM: R101.1, U14.9 (ILM)
/E28_ANA_2_DVDT: R118.1, U32.7 (DVDT)
/E28_ANA_2_DVDT_CAP: C49.1, R118.2
/E28_ANA_2_ILM: R117.1, U32.9 (ILM)
/E28_ANA_ENABLE: R96.1, U13.1 (EN_UVLO), U30.3 (Y)
/E28_ANA_FOLLOW: R100.1, U14.1 (EN_UVLO), U31.7 (Y)
/E28_ANA_FOLLOW2: R116.1, U32.1 (EN_UVLO), U34.3 (Y)
/E28_ANA_OUT_SENSE: C55.1, R129.2, R130.1, U18.9 (SENSE+)
/E28_ANA_SRC_SENSE: C53.1, R123.2, R124.1, U18.5 (SENSE+)
/E28_ARMED: U21.3 (B), U21.4 (Y), U25.9 (A)
/E28_ARM_BAR: U21.1 (Y), U21.6 (B)
/E28_AUX_CT: C60.1, U19.5 (CT)
/E28_AUX_DIV: R137.2, R138.1
/E28_AUX_RESET_N: U31.5 (A), U35.5 (2Y)
/E28_AUX_RESET_RAW: R135.1, U19.6 (RESET_N), U35.3 (2A)
/E28_AUX_SENSE: R138.2, R139.1, U19.1 (SENSE)
/E28_AUX_VALID: U24.13 (B), U28.3 (A), U29.2 (B), U31.3 (Y)
/E28_DIG_0_DVDT: R106.1, U15.7 (DVDT)
/E28_DIG_0_DVDT_CAP: C43.1, R106.2
/E28_DIG_0_ILM: R105.1, U15.9 (ILM)
/E28_DIG_1_DVDT: R110.1, U16.7 (DVDT)
/E28_DIG_1_DVDT_CAP: C45.1, R110.2
/E28_DIG_1_ILM: R109.1, U16.9 (ILM)
/E28_DIG_2_DVDT: R114.1, U17.7 (DVDT)
/E28_DIG_2_DVDT_CAP: C47.1, R114.2
/E28_DIG_2_ILM: R113.1, U17.9 (ILM)
/E28_DIG_3_DVDT: R122.1, U33.7 (DVDT)
/E28_DIG_3_DVDT_CAP: C51.1, R122.2
/E28_DIG_3_ILM: R121.1, U33.9 (ILM)
/E28_DIG_FOLLOW1: R108.1, U16.1 (EN_UVLO), U29.3 (Y)
/E28_DIG_FOLLOW2: R112.1, U17.1 (EN_UVLO), U30.7 (Y)
/E28_DIG_FOLLOW3: R120.1, U33.1 (EN_UVLO), U34.7 (Y)
/E28_DIG_OUT_SENSE: C56.1, R132.2, R133.1, U18.11 (SENSE+)
/E28_DIG_SRC_SENSE: C54.1, R126.2, R127.1, U18.7 (SENSE+)
/E28_FAULT: J9.4 (E28_FAULT), U21.9 (B), U21.13 (Y), U23.5 (B), U28.5 (A)
/E28_FAULT_A: U23.8 (Y), U23.12 (A)
/E28_FAULT_ANY: U23.11 (Y), U25.10 (B)
/E28_FAULT_BAR: U21.10 (Y), U21.12 (B)
/E28_FAULT_SET: U21.8 (A), U25.8 (Y)
/E28_MASTER_ENABLE: J6.2 (ALL_RAILS_ALLOW), J9.5 (E28_MASTER_ENABLE), R4.1, R12.1, R20.1, R28.1, R104.1, R141.1, U15.1 (EN_UVLO), U20.1 (SENSE), U20.3 (MR_N), U25.13 (B), U27.2 (B), U29.5 (A), U29.7 (Y), U30.1 (A), U30.5 (A), U31.1 (A), U34.2 (B), U34.5 (A)
/E28_NORMAL_OK: U22.8 (A), U27.8 (Y)
/E28_NORMAL_PRE: U24.8 (Y), U27.9 (A)
/E28_NOT_AUX: U23.2 (B), U28.4 (Y)
/E28_NOT_FAULT: U27.13 (B), U28.6 (Y)
/E28_NOT_NORMAL_OK: U22.10 (Y), U23.9 (A)
/E28_NOT_OUT_READY: U22.13 (Y), U26.2 (B), U26.5 (B)
/E28_NOT_RUN: U23.1 (A), U28.2 (Y), U28.9 (A)
/E28_NOT_SOURCE_READY: U28.10 (Y), U28.13 (A)
/E28_OUTPUT_PERMISSION: U26.11 (Y), U27.1 (A)
/E28_OUTPUT_READY: J9.3 (E28_OUTPUT_READY), U25.6 (Y)
/E28_OUT_ARMED: U22.3 (B), U22.4 (Y), U26.1 (A)
/E28_OUT_ARM_BAR: U22.1 (Y), U22.6 (B)
/E28_OUT_READY: U22.11 (A), U24.6 (Y), U25.12 (A), U26.13 (B)
/E28_OUT_UV_FAULT: U23.10 (B), U26.3 (Y)
/E28_OUT_VALID_ACTIVE: U22.2 (A), U25.11 (Y)
/E28_RESET: U21.5 (A), U21.11 (A), U23.3 (Y), U23.4 (A)
/E28_RESET_OUT: U22.5 (A), U23.6 (Y)
/E28_RUN_AND_SOURCE: U24.12 (A), U27.6 (Y)
/E28_RUN_LOGIC: U27.4 (A), U28.8 (Y)
/E28_SAFE_REQUEST: R140.1, U12.13 (4B), U27.11 (Y)
/E28_SAFE_STAGE: U25.3 (Y), U27.12 (A)
/E28_SOURCE_READY: U24.3 (Y), U24.9 (A), U25.2 (B)
/E28_SOURCE_READY_LOGIC: U27.5 (B), U27.10 (B), U28.12 (Y)
/E28_TIMEOUT: U26.4 (A), U35.7 (1Y)
/E28_TIMEOUT_CT: C61.1, C62.1, C63.1, C64.1, C65.1, U20.5 (CT)
/E28_TIMEOUT_FAULT: U23.13 (B), U26.6 (Y)
/E28_TIMEOUT_RAW: R136.1, U20.6 (RESET_N), U35.1 (1A)
/E28_USER_AUX: U24.11 (Y), U25.1 (A)
/N12: C16.2, J3.5 (N12), Q8.3 (DRAIN_GROUP), R31.1, R32.1
/N12_ALLOW: R28.2, R29.1, U4.3 (IN)
/N12_COMMON: Q7.1 (SOURCE_GROUP), Q8.1 (SOURCE_GROUP), R26.2, U4.5 (SOURCE)
/N12_DRIVE: R25.1, U4.8 (GATE)
/N12_GATE: Q7.2 (GATE_GROUP), Q8.2 (GATE_GROUP), R25.2, R26.1
/N12_INV: R54.1, R55.1, U8.7 (OUT_B)
/N12_MCAP1: C14.2, U4.7 (MCAP1)
/N12_MCAP1_LIMIT: C14.1, R30.2
/N12_MCAP2: C15.2, U4.6 (MCAP2)
/N12_MCAP2_LIMIT: C15.1, R31.2
/N12_OV_OK: R71.1, R72.2, U9.13 (4OUT), U37.1 (1A)
/N12_OV_OK_SCHMITT: U11.4 (2A), U37.7 (1Y)
/N12_OV_REF: R70.2, R71.2, U9.11 (4+)
/N12_OV_SENSE: C28.1, R55.2, U9.10 (4-)
/N12_SRC: J1.5 (N12_SRC), Q7.3 (DRAIN_GROUP), R30.1, R53.1
/N12_SUM: R53.2, R54.2, U8.6 (IN-_B)
/N12_TT: R27.1, U4.2 (TT)
/N19: C8.2, J3.3 (N19), Q4.3 (DRAIN_GROUP), R15.1, R16.1
/N19_ALLOW: R12.2, R13.1, U2.3 (IN)
/N19_COMMON: Q3.1 (SOURCE_GROUP), Q4.1 (SOURCE_GROUP), R10.2, U2.5 (SOURCE)
/N19_DRIVE: R9.1, U2.8 (GATE)
/N19_GATE: Q3.2 (GATE_GROUP), Q4.2 (GATE_GROUP), R9.2, R10.1
/N19_INPUT_MID: R49.2, R50.1
/N19_INV: R51.1, R52.1, U8.1 (OUT_A)
/N19_MCAP1: C6.2, U2.7 (MCAP1)
/N19_MCAP1_LIMIT: C6.1, R14.2
/N19_MCAP2: C7.2, U2.6 (MCAP2)
/N19_MCAP2_LIMIT: C7.1, R15.2
/N19_OV_OK: R63.1, R64.2, U9.1 (2OUT), U36.3 (2A)
/N19_OV_OK_SCHMITT: U11.1 (1A), U36.5 (2Y)
/N19_OV_REF: R62.2, R63.2, U9.7 (2+)
/N19_OV_SENSE: C27.1, R52.2, U9.6 (2-)
/N19_SRC: J1.3 (N19_SRC), Q3.3 (DRAIN_GROUP), R14.1, R49.1
/N19_SUM: R50.2, R51.2, U8.2 (IN-_A)
/N19_TT: R11.1, U2.2 (TT)
/NF_OUTPUT_VALID_RAW: J12.1 (NF_OUTPUT_VALID_RAW), R143.1, U35.6 (3A)
/NF_VALID_LOGIC: U25.5 (B), U35.2 (3Y)
/OK_5: U11.8 (3Y), U12.4 (2A)
/OK_12: U11.6 (2Y), U12.2 (1B)
/OK_19: U11.3 (1Y), U12.1 (1A)
/OK_ALL_OV: U12.8 (3Y), U12.12 (4A), U24.10 (B)
/OK_ANALOG: U12.3 (1Y), U12.9 (3A)
/OK_AUXILIARY: U12.6 (2Y), U12.10 (3B)
/OK_REF: U11.11 (4Y), U12.5 (2B)
/P03_SOURCES_READY: J9.2 (P03_SOURCES_READY), R142.1, U28.11 (A)
/P12: C12.1, J3.4 (P12), Q6.3 (DRAIN_GROUP), R23.1, R24.1
/P12_ALLOW: R20.2, R21.1, U3.3 (IN)
/P12_COMMON: Q5.1 (SOURCE_GROUP), Q6.1 (SOURCE_GROUP), R18.2, U3.5 (SOURCE)
/P12_DRIVE: R17.1, U3.8 (GATE)
/P12_GATE: Q5.2 (GATE_GROUP), Q6.2 (GATE_GROUP), R17.2, R18.1
/P12_MCAP1: C10.2, U3.7 (MCAP1)
/P12_MCAP1_LIMIT: C10.1, R22.2
/P12_MCAP2: C11.2, U3.6 (MCAP2)
/P12_MCAP2_LIMIT: C11.1, R23.2
/P12_OV_OK: R68.1, R69.2, U9.14 (3OUT), U36.6 (3A)
/P12_OV_OK_SCHMITT: U11.5 (2B), U36.2 (3Y)
/P12_OV_REF: R67.2, R68.2, U9.9 (3+)
/P12_OV_SENSE: C31.1, R65.2, R66.1, U9.8 (3-)
/P12_SRC: J1.4 (P12_SRC), Q5.3 (DRAIN_GROUP), R22.1, R65.1
/P12_TT: R19.1, U3.2 (TT)
/P19: C4.1, J3.1 (P19), Q2.3 (DRAIN_GROUP), R7.1, R8.1
/P19_ALLOW: R4.2, R5.1, U1.3 (IN)
/P19_COMMON: Q1.1 (SOURCE_GROUP), Q2.1 (SOURCE_GROUP), R2.2, U1.5 (SOURCE)
/P19_DRIVE: R1.1, U1.8 (GATE)
/P19_GATE: Q1.2 (GATE_GROUP), Q2.2 (GATE_GROUP), R1.2, R2.1
/P19_MCAP1: C2.2, U1.7 (MCAP1)
/P19_MCAP1_LIMIT: C2.1, R6.2
/P19_MCAP2: C3.2, U1.6 (MCAP2)
/P19_MCAP2_LIMIT: C3.1, R7.2
/P19_OV_OK: R60.1, R61.2, U9.2 (1OUT), U36.1 (1A)
/P19_OV_OK_SCHMITT: U11.2 (1B), U36.7 (1Y)
/P19_OV_REF: R59.2, R60.2, U9.5 (1+)
/P19_OV_SENSE: C30.1, R57.2, R58.1, U9.4 (1-)
/P19_SENSE_MID: R56.2, R57.1
/P19_SRC: J1.1 (P19_SRC), Q1.3 (DRAIN_GROUP), R6.1, R56.1
/P19_TT: R3.1, U1.2 (TT)
/POS_OUTPUT_READY: U25.4 (A), U27.3 (Y)
/POWER_RUN: J5.3 (POWER_RUN), R93.1, U43.2 (A)
/PROTECT_REF: C26.1, J6.3 (PROTECT_REF), R59.1, R62.1, R67.1, R70.1, R75.1, R80.1, R85.1, R94.1, U7.6 (VREF), U10.10 (4-), U18.4 (REF-), U18.6 (REF-), U18.8 (REF-), U18.10 (REF-)
/REF_HIGH_AUX: R88.2, R89.1, R90.1
/REF_HIGH_OK: R91.1, R92.2, U10.13 (4OUT), U38.3 (2A)
/REF_HIGH_OK_SCHMITT: U11.13 (4B), U38.5 (2Y)
/REF_HIGH_POSITIVE: R90.2, R91.2, U10.11 (4+)
/REF_LOW_AUX: R83.2, R84.1, U10.8 (3-)
/REF_LOW_OK: R86.1, R87.2, U10.14 (3OUT), U38.1 (1A)
/REF_LOW_OK_SCHMITT: U11.12 (4A), U38.7 (1Y)
/REF_LOW_POSITIVE: R85.2, R86.2, U10.9 (3+)
/RUN_BUFFERED: U28.1 (A), U43.4 (Y)
/V2V5_AUX: C1.1, C5.1, C9.1, C13.1, C17.1, C21.1, C25.1, C29.1, C34.1, C35.1, C36.1, C37.1, C38.1, C57.1, C58.1, C59.1, C66.1, C67.1, C68.1, C69.1, C70.1, C71.1, C72.1, C73.1, C74.1, C75.1, C76.1, C77.1, C78.1, C79.1, C80.1, C81.1, C82.1, C83.1, C84.1, C85.1, C86.1, J5.1 (V2V5_AUX), R61.1, R64.1, R69.1, R72.1, R77.1, R82.1, R83.1, R87.1, R88.1, R92.1, R95.2, R99.2, R103.2, R107.2, R111.2, R115.2, R119.2, R125.1, R128.1, R131.1, R134.1, R135.2, R136.2, R137.1, U1.1 (VDD), U2.1 (VDD), U3.1 (VDD), U4.1 (VDD), U7.3 (EN), U7.4 (VIN), U8.8 (V+), U9.3 (V+), U10.3 (V+), U11.14 (VCC), U12.14 (VCC), U18.3 (V+), U19.3 (MR_N), U19.4 (VDD), U20.4 (VDD), U21.14 (VCC), U22.14 (VCC), U23.14 (VCC), U24.14 (VCC), U25.14 (VCC), U26.14 (VCC), U27.14 (VCC), U28.14 (VCC), U29.8 (VCC), U30.8 (VCC), U31.6 (B), U31.8 (VCC), U34.8 (VCC), U35.8 (VCC), U36.8 (VCC), U37.8 (VCC), U38.8 (VCC), U39.8 (VCC), U40.8 (VCC), U41.8 (VCC), U42.8 (VCC), U43.5 (VCC)
/V5_REG: C20.1, J3.6 (V5_REG), R40.1, R129.1, U13.6 (OUT), U13.11 (OUT), U14.6 (OUT), U14.11 (OUT), U32.6 (OUT), U32.11 (OUT)
/V5_REG_OV_OK: R76.1, R77.2, U10.2 (1OUT), U37.3 (2A)
/V5_REG_OV_OK_SCHMITT: U11.9 (3A), U37.5 (2Y)
/V5_REG_OV_REF: R75.2, R76.2, U10.5 (1+)
/V5_REG_OV_SENSE: C32.1, R73.2, R74.1, U10.4 (1-)
/V5_REG_SRC: C40.1, C42.1, C50.1, J1.6 (V5_REG_SRC), J10.1, R73.1, R123.1, U13.5 (IN), U13.12 (IN), U14.5 (IN), U14.12 (IN), U32.5 (IN), U32.12 (IN)

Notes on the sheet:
E28LP: Eight AUPDCU triples + highimpedanceRUN receiver; no original force/timing/reference or latch topology change.
The full271part circuit is a new prototype. All actual-band threshold/current, completehousing, startup and physical gates remain unqualified.

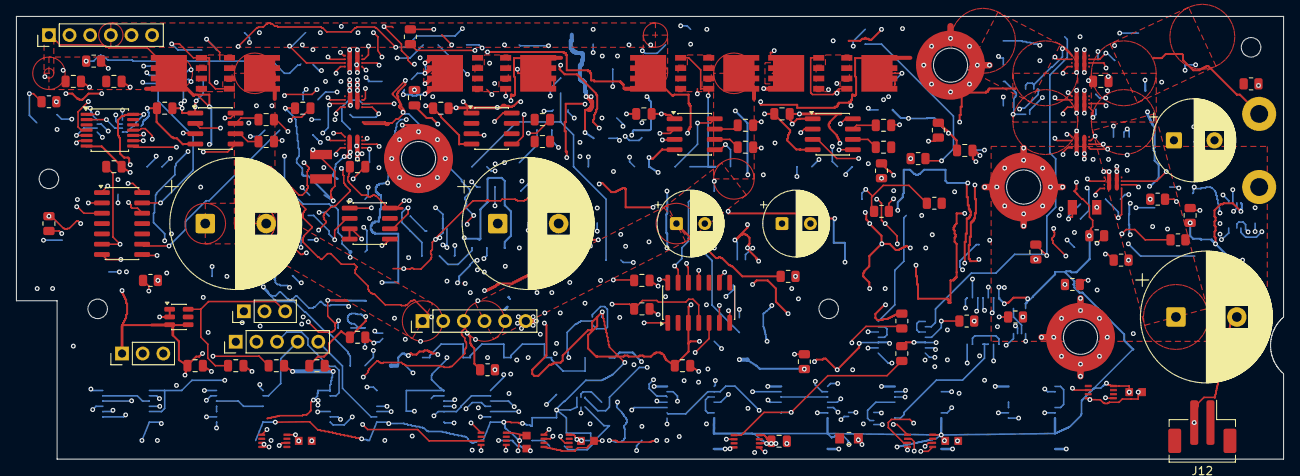
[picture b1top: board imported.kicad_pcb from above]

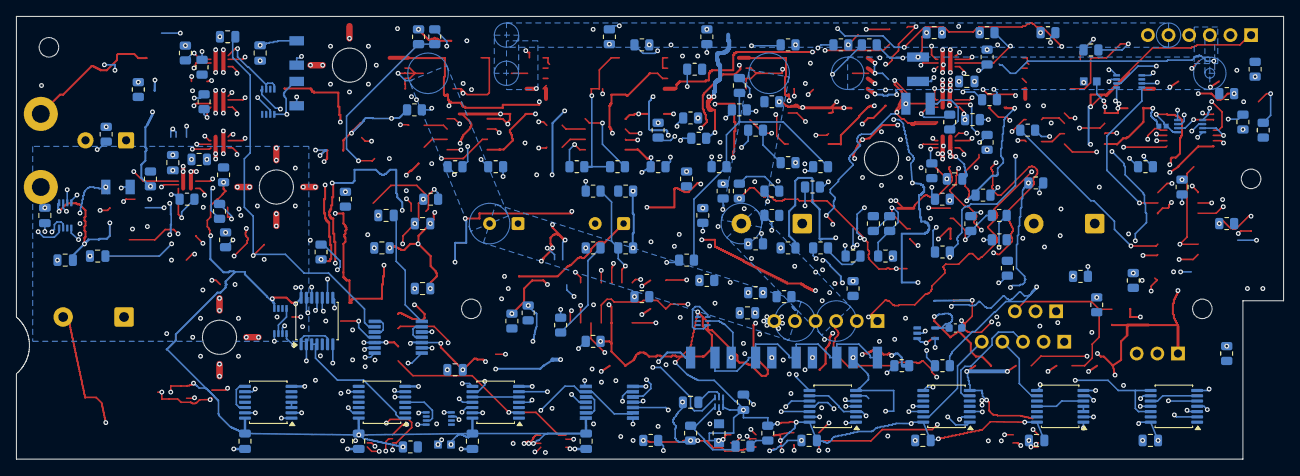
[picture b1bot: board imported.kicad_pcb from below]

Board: 8 copper layers, 156.0 x 54.5 mm, 275 parts (162 on the bottom side), 199 nets.

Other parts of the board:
H1, H2, H3, H4: M2_CLEARANCE; M2_Clearance
